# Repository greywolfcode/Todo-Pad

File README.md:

# Todo Pad
Todo Pad (from the spanish "Todo" meaning all), is a macropad set up to type any Unicode charachter.

## CAD
The lid is designed to attach with a friction fit to allow it to be removed, and the case is angled at 5 degrees. 

Note that case.step has just the case models, whereas full_model.step is the assembled model with PCB.

## PCB
The PCB was designed in KiCad.
This is the schematic:

And here is the PCB:

## Firmware
Todo pad is controlled using [KMK](https://github.com/KMKfw/kmk_firmware). It has functionality for Unicode and three seperate key layers. A keys.keyconfig file is used to store layouts, and an example is provided with the firmware.

### Layout Editor
The layout editor provides a way to create the keys.keyconfig files used to define the key layouts for the Todo Pad. It is not the most complicated program, but it works.

## Bill of Materials
- XIAO RP2040: 1x
- Cherry MX Switches: 14x
- White DSA Keycaps: 14x
- 1N4148 Diodes: 14x
- SSD1306 0.91" 128x32 OLED Display: 1x
- PCB: 1x
- 3D Printed Case: 1x

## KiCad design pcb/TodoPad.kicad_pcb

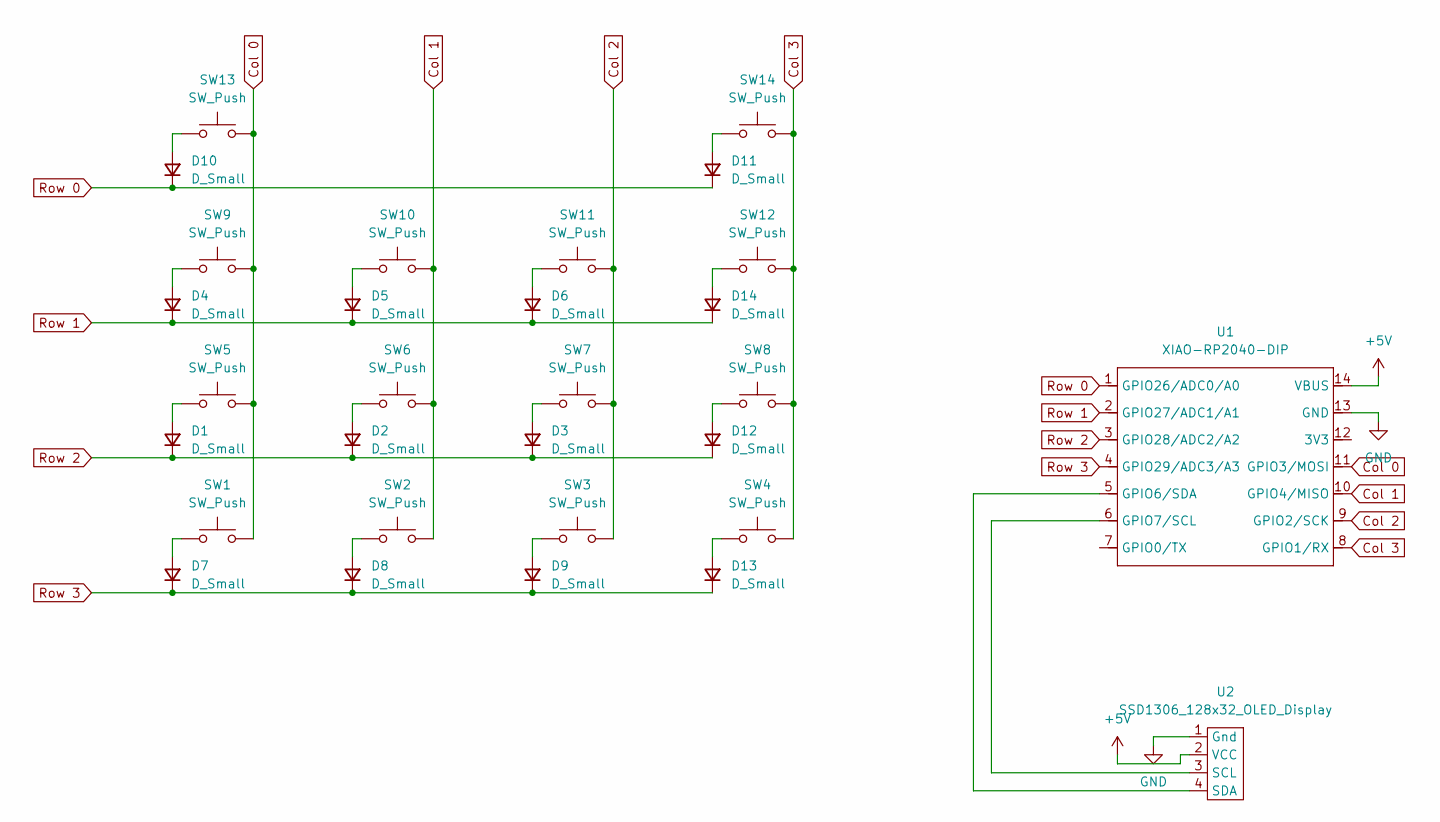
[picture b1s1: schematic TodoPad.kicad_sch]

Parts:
D1, D2, D3, D4, D5, D6, D7, D8, D9, D10, D11, D12, D13, D14: D_Small; D_DO-35_SOD27_P7.62mm_Horizontal
SW1, SW2, SW3, SW4, SW5, SW6, SW7, SW8, SW9, SW10, SW11, SW12, SW13, SW14: SW_Push; SW_Cherry_MX_1.00u_PCB
U1: XIAO-RP2040-DIP
U2: SSD1306_128x32_OLED_Display; SSD1306-0.91-OLED-4pin-128x32

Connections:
+5V: U1.14 (VBUS), U2.2 (VCC)
Col 0: SW1.2, SW5.2, SW9.2, SW13.2, U1.11 (GPIO3/MOSI)
Col 1: SW2.2, SW6.2, SW10.2, U1.10 (GPIO4/MISO)
Col 2: SW3.2, SW7.2, SW11.2, U1.9 (GPIO2/SCK)
Col 3: SW4.2, SW8.2, SW12.2, SW14.2, U1.8 (GPIO1/RX)
GND: U1.13 (GND), U2.1 (Gnd)
unnamed: D1.2 (A), SW5.1
unnamed: D2.2 (A), SW6.1
unnamed: D3.2 (A), SW7.1
unnamed: D4.2 (A), SW9.1
unnamed: D5.2 (A), SW10.1
unnamed: D6.2 (A), SW11.1
unnamed: D7.2 (A), SW1.1
unnamed: D8.2 (A), SW2.1
unnamed: D9.2 (A), SW3.1
unnamed: D10.2 (A), SW13.1
unnamed: D11.2 (A), SW14.1
unnamed: D12.2 (A), SW8.1
unnamed: D13.2 (A), SW4.1
unnamed: D14.2 (A), SW12.1
unnamed: U1.5 (GPIO6/SDA), U2.4 (SDA)
unnamed: U1.6 (GPIO7/SCL), U2.3 (SCL)
Row 0: D10.1 (K), D11.1 (K), U1.1 (GPIO26/ADC0/A0)
Row 1: D4.1 (K), D5.1 (K), D6.1 (K), D14.1 (K), U1.2 (GPIO27/ADC1/A1)
Row 2: D1.1 (K), D2.1 (K), D3.1 (K), D12.1 (K), U1.3 (GPIO28/ADC2/A2)
Row 3: D7.1 (K), D8.1 (K), D9.1 (K), D13.1 (K), U1.4 (GPIO29/ADC3/A3)

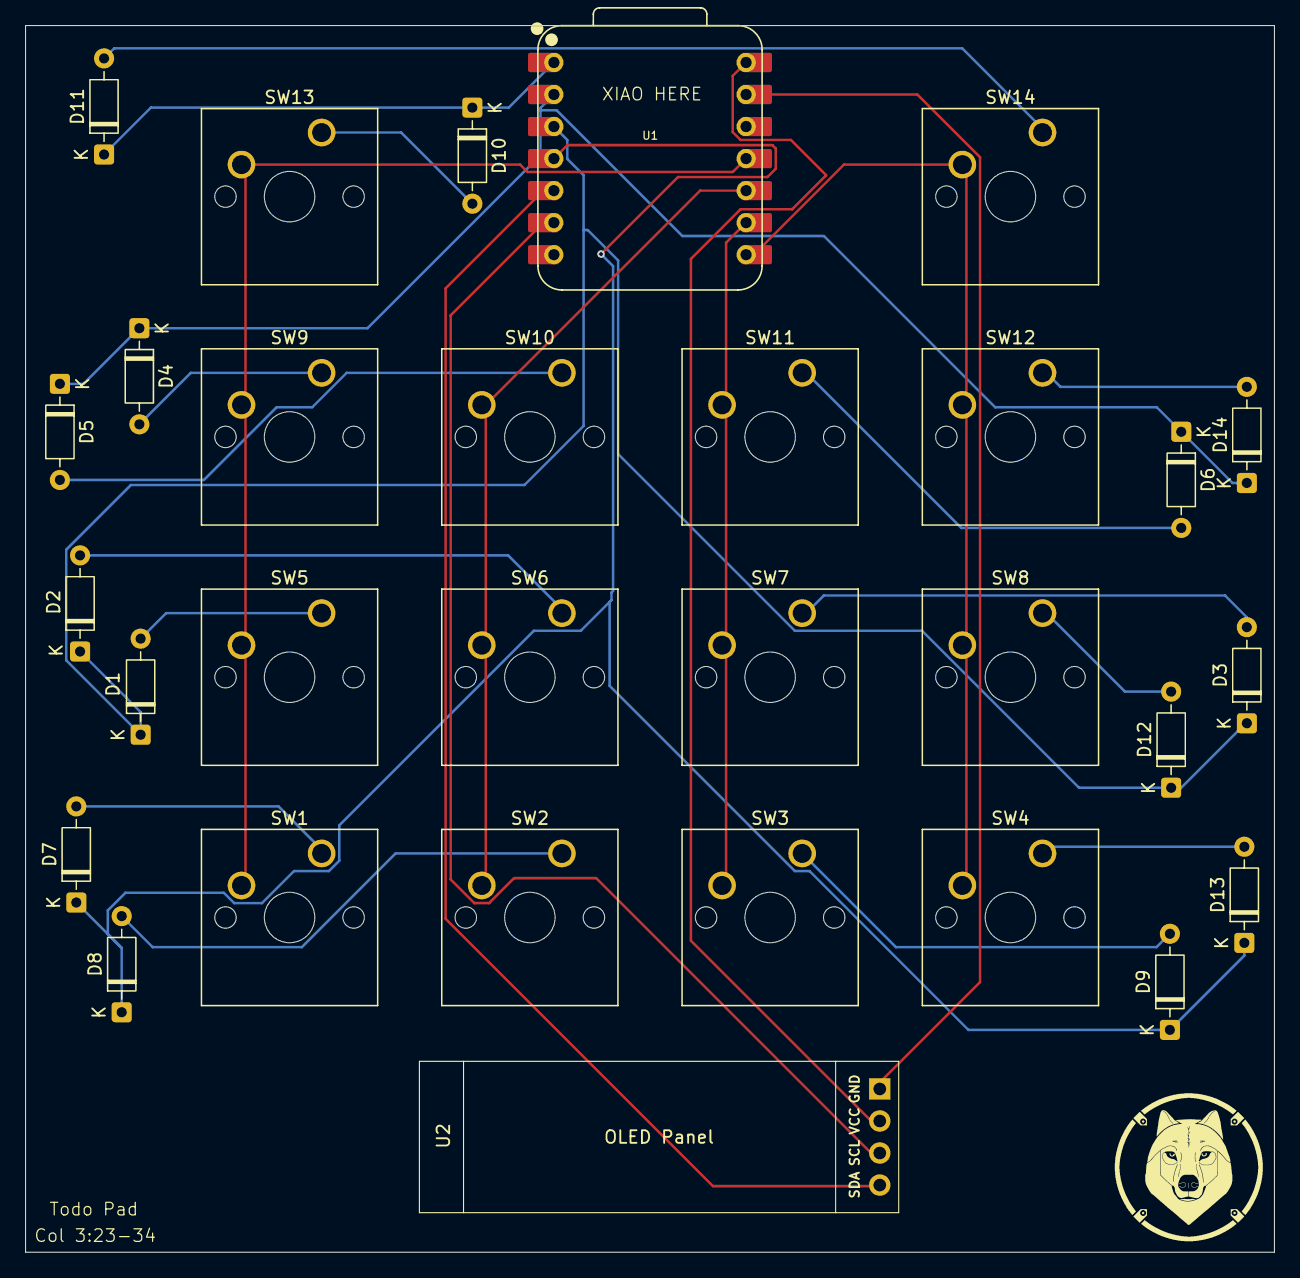
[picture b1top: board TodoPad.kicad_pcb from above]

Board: 2 copper layers, 99.0 x 97.2 mm, 30 parts (0 on the bottom side), 26 nets.

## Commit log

2025-11-27 Added necessary KiCad libraries
2025-11-28 Rename CadaPad to Todo Pad in README
2025-11-28 Started Schematic
2025-11-28 Made KiCad symbol for OLED display
2025-11-28 Wired up buttons on schematic
2025-11-28 Add the correct number of buttons, updated footprint assignment
2025-11-28 Schematic is done and pcb is organised
2025-11-28 Started routing PCB
2025-11-28 Routing first attempt is complete
2025-11-28 Add decorations and branding to PCB
2025-11-28 Centred PCB components, started case model
2025-11-29 Finished case model
2025-11-29 Started firmware
2025-11-30 Added components to firmware, started editor
2025-11-30 Layout editor now has buttons
2025-11-30 Layout editor now can produce .keyconfig files
2025-11-30 Firmware almost done
2025-12-01 Firmware done
2025-12-01 Finalised everything
2025-12-01 Fixed formatting of diodes in README.
2025-12-01 Updated editor.py
2025-12-02 Modified PCB for production
2025-12-02 Gerbers are in a folder not zip, and now contain drill files
2025-12-02 Gerbers did not need to be in two folders
2025-12-27 Made loading files into editor work, made editor more suer friendly, and added example keys.keyconfig file
2025-12-27 Fixed a few errors in main.py
2025-12-27 Update firmware explination
